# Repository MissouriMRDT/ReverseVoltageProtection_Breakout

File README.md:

# ReverseVoltageProtection_Breakout
Hardware for attachable reverse voltage protection circuit.

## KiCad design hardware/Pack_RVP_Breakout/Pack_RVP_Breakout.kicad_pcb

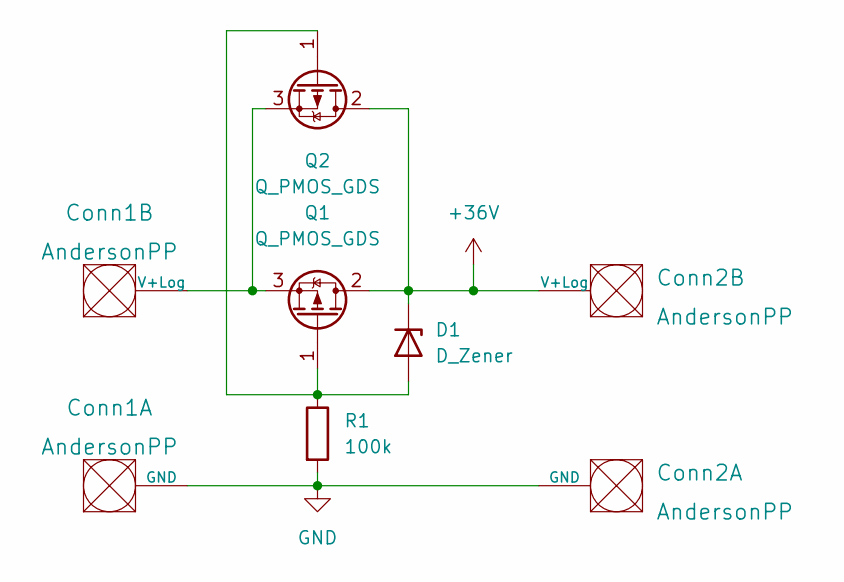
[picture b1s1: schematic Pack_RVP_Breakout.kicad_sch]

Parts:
Conn1, Conn2: AndersonPP; Square_Anderson_2_V_Side_By_Side
D1: D_Zener; SOT-23_Diode
Q1, Q2: Q_PMOS_GDS; TO-252-3_TabPin2
R1: 100k; R_0603_1608Metric_Pad0.98x0.95mm_HandSolder

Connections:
+36V: Conn2.2 (V+Log), D1.1 (K), Q1.2 (D), Q2.2 (D)
GND: Conn1.1 (GND), Conn2.1 (GND), R1.2
unnamed: Conn1.2 (V+Log), Q1.3 (S), Q2.3 (S)
unnamed: D1.2 (A), Q1.1 (G), Q2.1 (G), R1.1

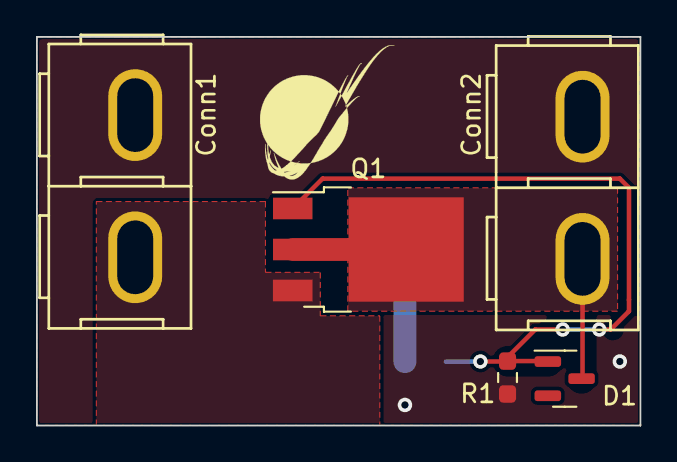
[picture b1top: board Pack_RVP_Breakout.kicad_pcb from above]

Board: 2 copper layers, 33.5 x 21.6 mm, 6 parts (1 on the bottom side), 4 nets.

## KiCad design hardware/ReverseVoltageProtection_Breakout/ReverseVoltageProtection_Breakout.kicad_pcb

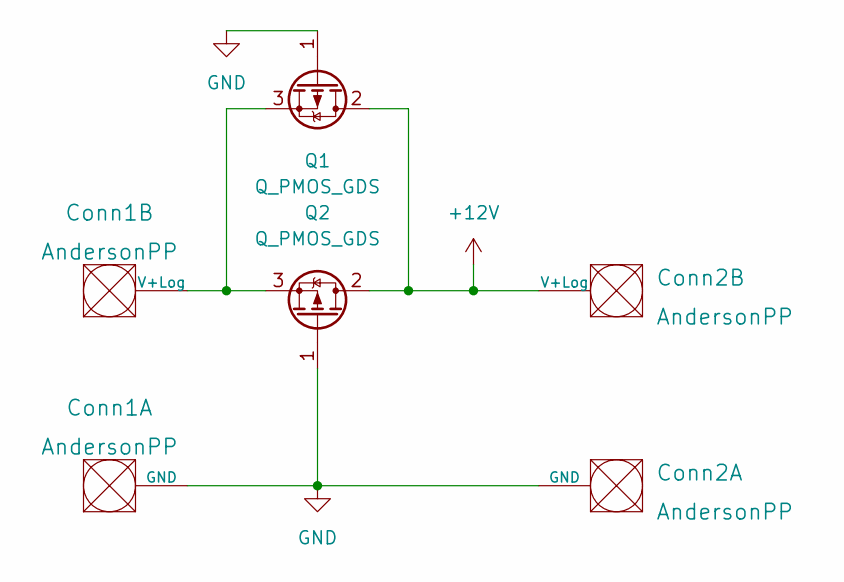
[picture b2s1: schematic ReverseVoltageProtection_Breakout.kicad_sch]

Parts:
Conn1, Conn2: AndersonPP; Square_Anderson_2_V_Side_By_Side
Q1, Q2: Q_PMOS_GDS; TO-252-3_TabPin2

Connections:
+12V: Conn2.2 (V+Log), Q1.2 (D), Q2.2 (D)
GND: Conn1.1 (GND), Conn2.1 (GND), Q1.1 (G), Q2.1 (G)
unnamed: Conn1.2 (V+Log), Q1.3 (S), Q2.3 (S)

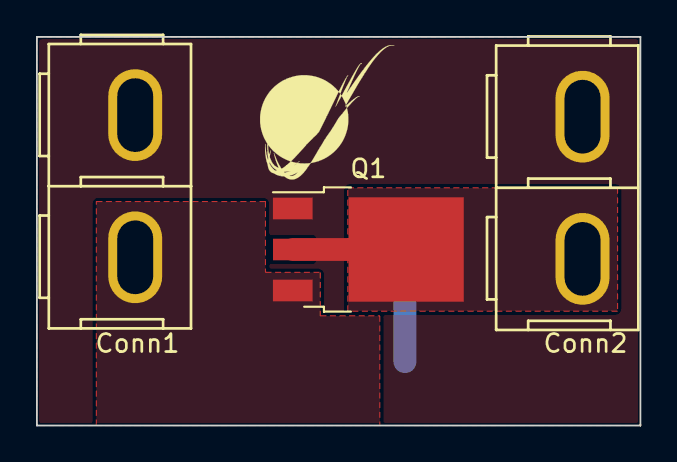
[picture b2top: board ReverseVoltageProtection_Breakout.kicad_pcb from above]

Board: 2 copper layers, 33.5 x 21.6 mm, 4 parts (1 on the bottom side), 3 nets.

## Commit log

2023-03-13 Designed 2oz board
2023-05-19 made 12V version
2023-05-19 Initial commit of pack version
2023-05-20 Made 30V version
2023-05-20 Modified trace widths
